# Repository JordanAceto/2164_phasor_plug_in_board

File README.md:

# NOTE: development of all VCF plug-in boards has been moved here https://github.com/JordanAceto/VCF_plug_in_boards
### This repo will no longer be updated. Follow the above link for the most current files.

# 2164 Phasor Plug-In Board

Small 6 stage SSM2164 based phase shifter PCB, designed to plug into a larger motherboard.

## Details

Six stage phase shifter implemented with SSM2164/V2164/SSI2164 quad VCAs. This PCB includes the audio path and CV inputs for frequency and feedback, but does not include any modulation sources.

The intended use for this board is to plug in to a larger motherboard which contains slots for two of these plug-in boards, as well as modulation sources, panel controls, and input/output routing. This motherboard could accept different filter boards sharing this footprint and header layout, for realizing stereo effects of various flavors.

## Inputs

-Audio in: dry audio input to be phase shifted.

-Frequency CV in: 0 volts to +2.048 volts, higher voltage = higher sweep.

-Feedback CV in: 0 volts to +2.048 volts, higher voltage = more feedback.

## Outputs

-Audio out: phase shifted audio output.

## Power Supply Requirements

A bipolar 12 volt power supply is needed. This will typically come from the motherboard.

## Calibration

-RV1 (depth trim): trims the depth of incoming frequency CV signals. Turn CW for greater depth and CCW for less depth. Adjust to taste.

-RV2 (center trim): trims the center frequency of the phase shifter. Turn CW for higher center frequency and CCW for lower center frequency. Adjust to taste.

-RV3 (feedback trim): trims the maximum amount of feedback. Turn CW for more maximum feedback and CCW for less maximum feedback. Exercise caution when adjusting this, as extreme settings can result in loud oscillations which could damage your ears or speakers if you are monitoring the sound with a loud amplifier. If you set this trimmer to be right on the edge of oscillation when about +2 volts is applied to the feedback CV input then make sure to sweep the frequency through its entire range, as a setting that doesn't squeal at certain frequency settings may squeal at other settings.

## Parts Ordering
The BOM has a link to a Mouser project with the majority of the parts needed to build the board, with the exception of the 2164 VCA chips. There is a link to the SmallBear Electronics parts page for these.

After the PCB is evaluated, the BOM will have a link to OSHPark, where you can order boards.

Zipped gerber files will be located in kicad_docs.

## License
CC by 4.0

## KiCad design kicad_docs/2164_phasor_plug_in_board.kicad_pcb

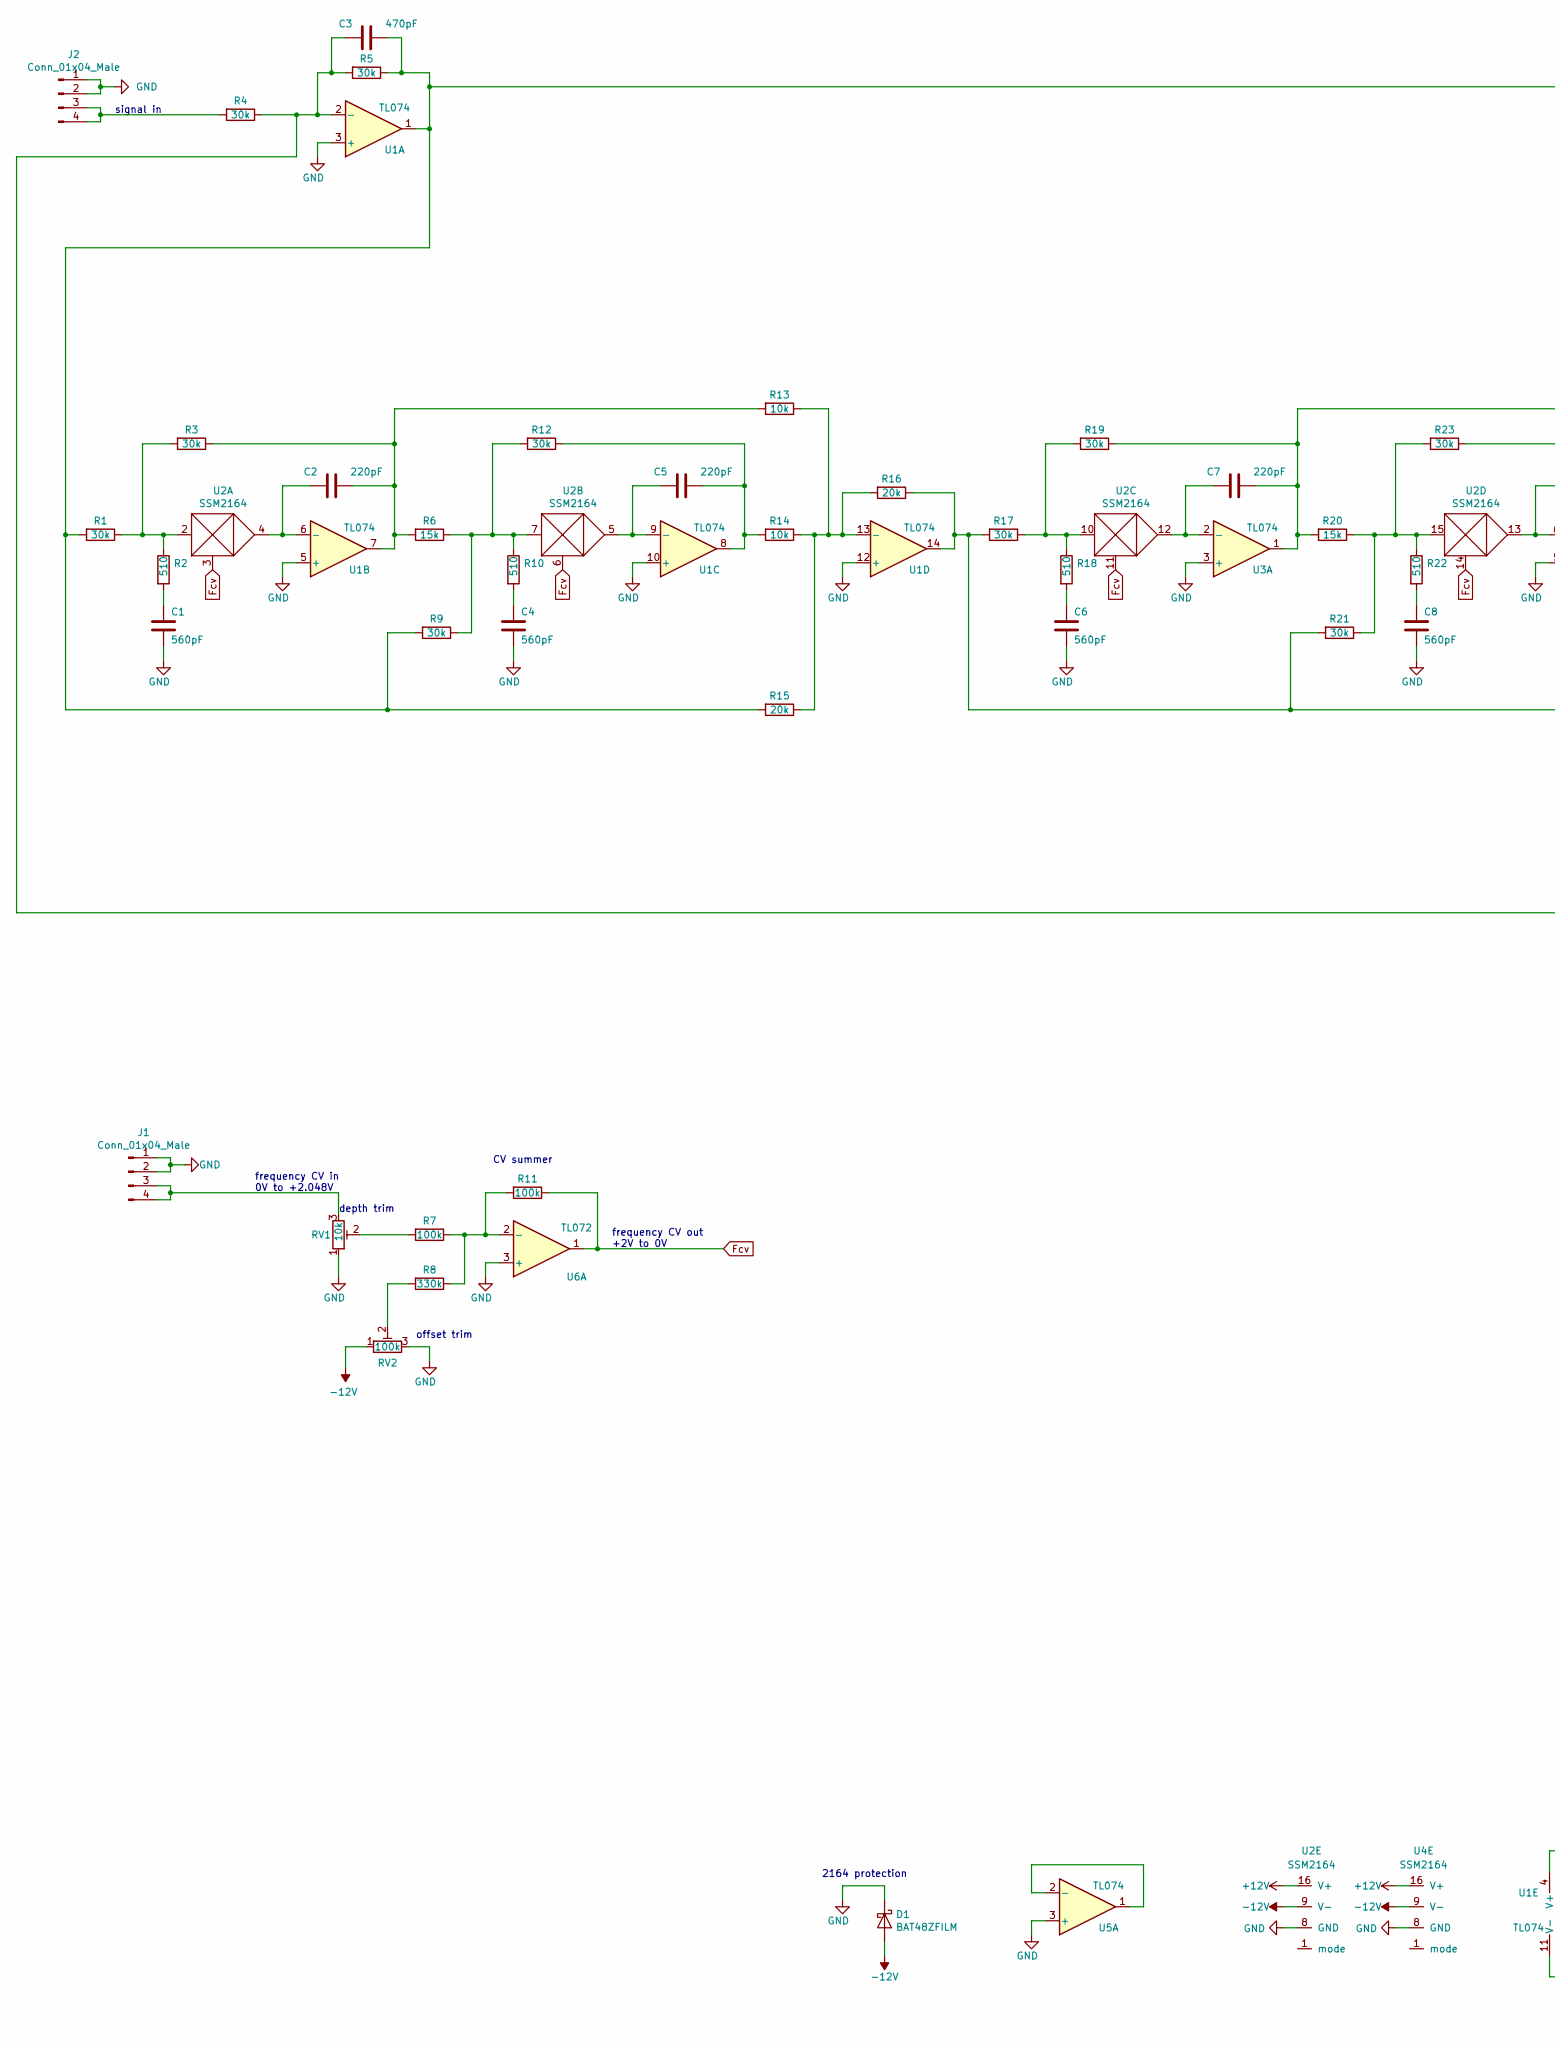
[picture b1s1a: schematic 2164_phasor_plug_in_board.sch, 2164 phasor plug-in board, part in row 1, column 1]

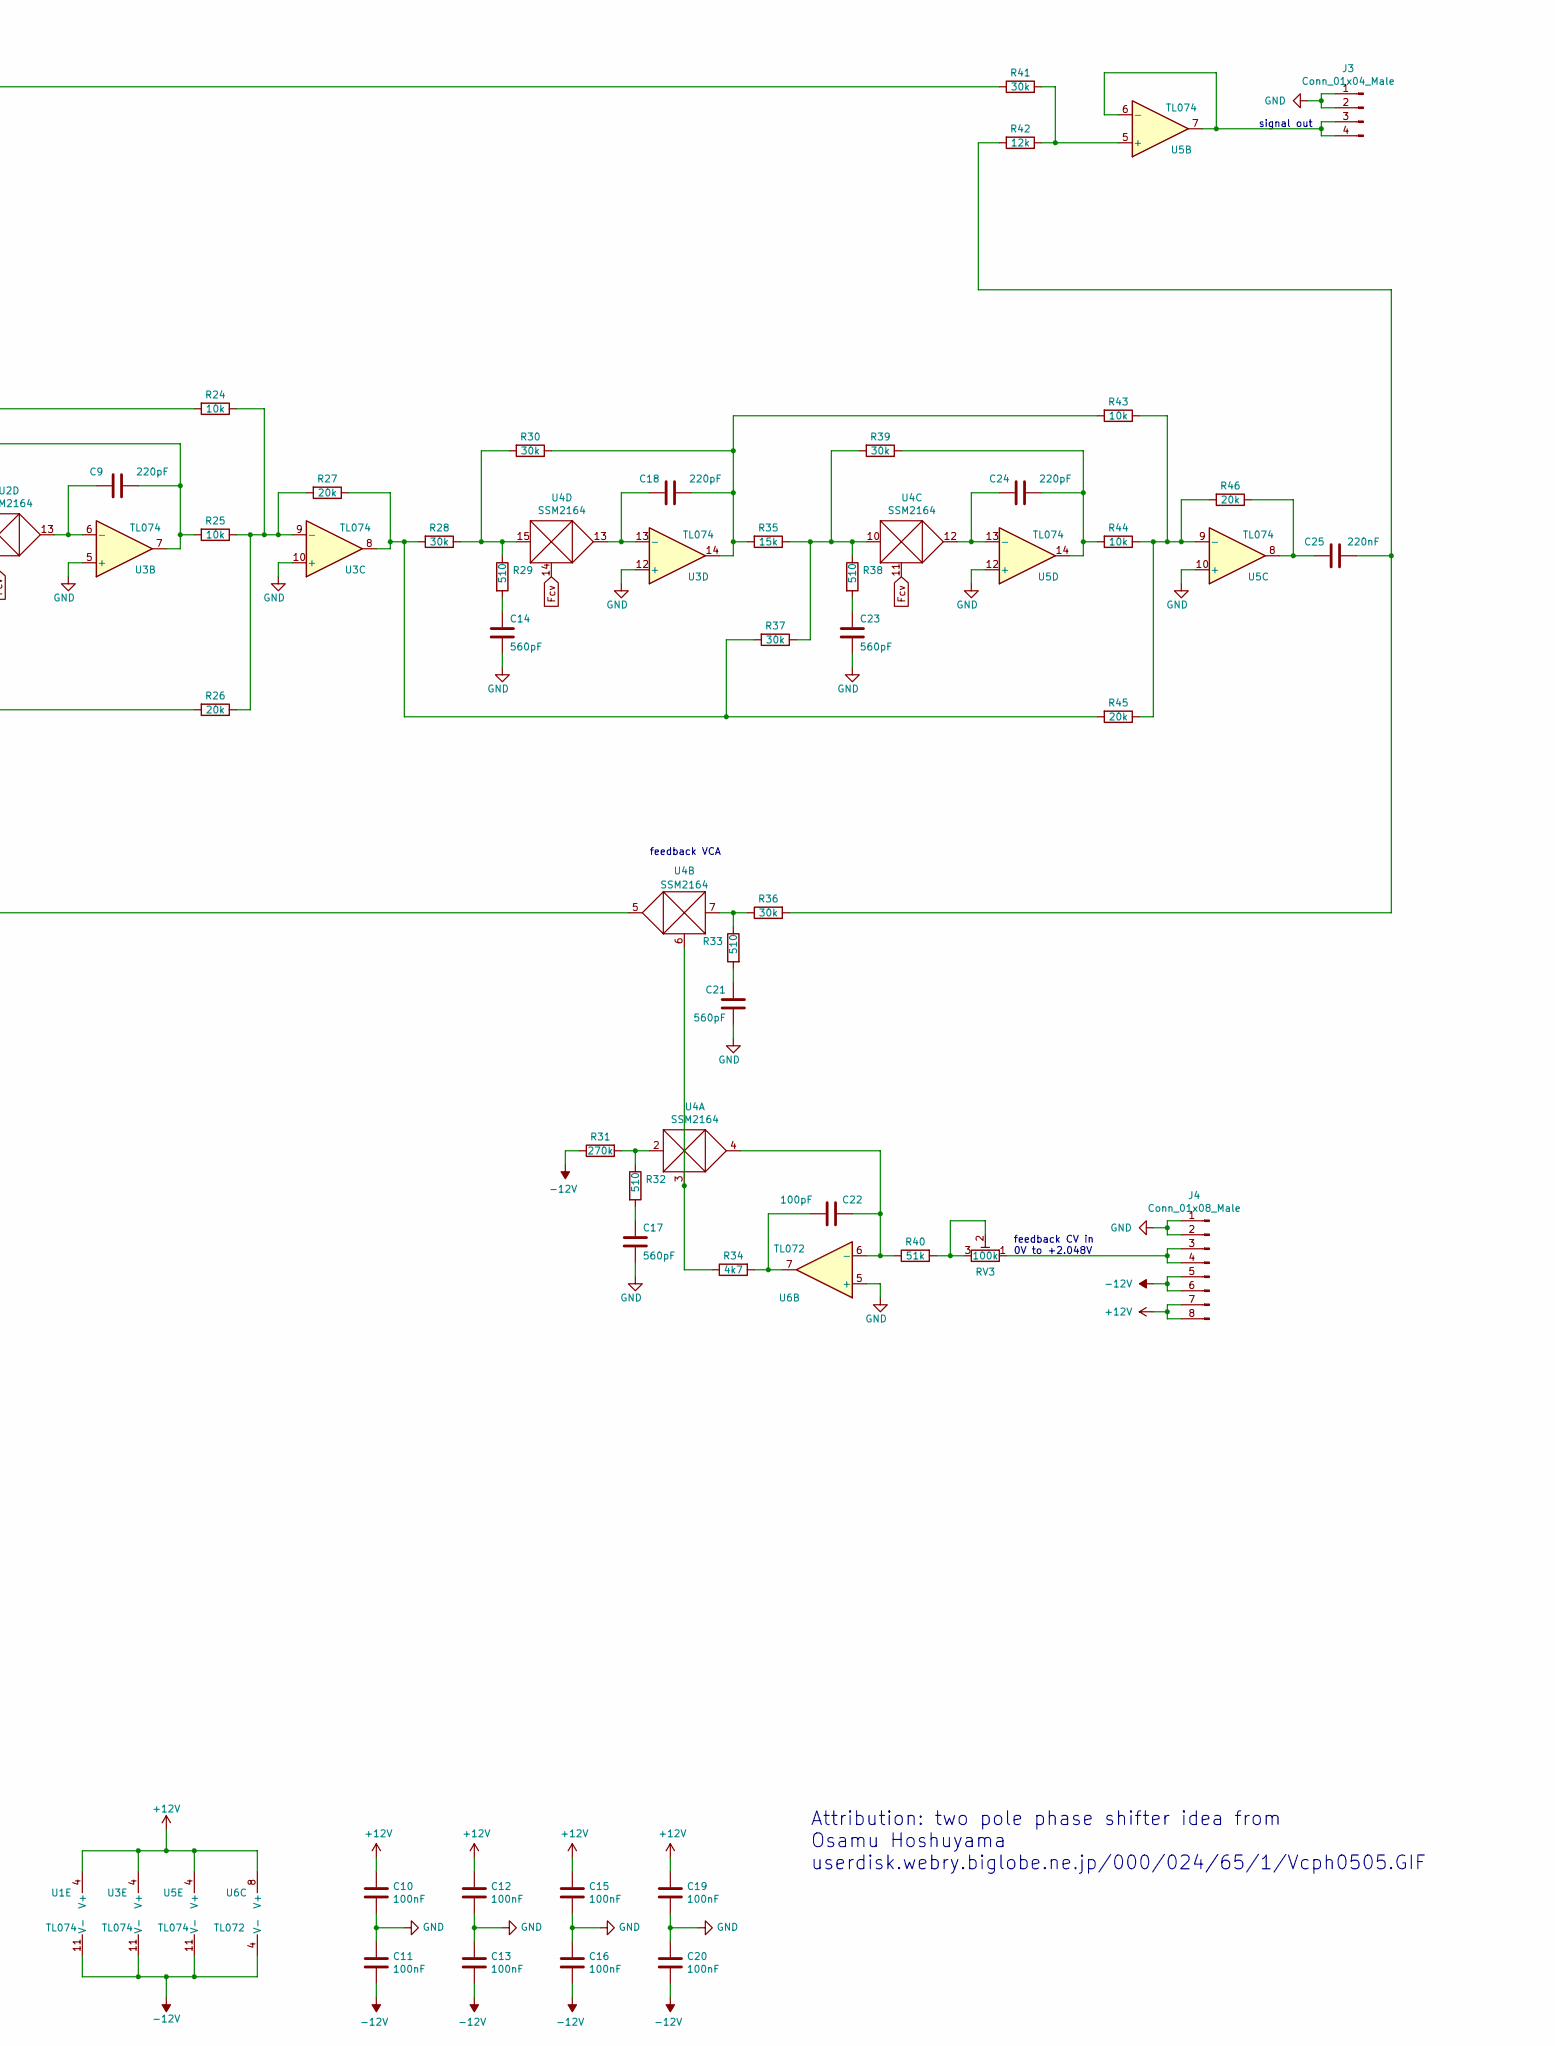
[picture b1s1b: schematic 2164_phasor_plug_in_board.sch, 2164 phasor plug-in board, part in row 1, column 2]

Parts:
C1, C4, C6, C8, C14, C17, C21, C23: 560pF; C_0805_2012Metric_Pad1.15x1.40mm_HandSolder
C2, C5, C7, C9, C18, C24: 220pF; C_0805_2012Metric_Pad1.15x1.40mm_HandSolder
C3: 470pF; C_0805_2012Metric_Pad1.15x1.40mm_HandSolder
C10, C11, C12, C13, C15, C16, C19, C20: 100nF; C_0805_2012Metric_Pad1.15x1.40mm_HandSolder
C22: 100pF; C_0805_2012Metric_Pad1.15x1.40mm_HandSolder
C25: 220nF; C_1206_3216Metric_Pad1.42x1.75mm_HandSolder
D1: BAT48ZFILM; D_SOD-123
J1, J2, J3: Conn_01x04_Male; PinHeader_1x04_P2.54mm_Vertical
J4: Conn_01x08_Male; PinHeader_1x08_P2.54mm_Vertical
R1, R3, R4, R5, R9, R12, R17, R19, R21, R23, R28, R30, R36, R37, R39, R41: 30k; R_0805_2012Metric_Pad1.15x1.40mm_HandSolder
R2, R10, R18, R22, R29, R32, R33, R38: 510; R_0805_2012Metric_Pad1.15x1.40mm_HandSolder
R6, R20, R35: 15k; R_0805_2012Metric_Pad1.15x1.40mm_HandSolder
R7, R11: 100k; R_0805_2012Metric_Pad1.15x1.40mm_HandSolder
R8: 330k; R_0805_2012Metric_Pad1.15x1.40mm_HandSolder
R13, R14, R24, R25, R43, R44: 10k; R_0805_2012Metric_Pad1.15x1.40mm_HandSolder
R15, R16, R26, R27, R45, R46: 20k; R_0805_2012Metric_Pad1.15x1.40mm_HandSolder
R31: 270k; R_0805_2012Metric_Pad1.15x1.40mm_HandSolder
R34: 4k7; R_0805_2012Metric_Pad1.15x1.40mm_HandSolder
R40: 51k; R_0805_2012Metric_Pad1.15x1.40mm_HandSolder
R42: 12k; R_0805_2012Metric_Pad1.15x1.40mm_HandSolder
RV1: 10k; Potentiometer_Bourns_3269W_Vertical
RV2, RV3: 100k; Potentiometer_Bourns_3269W_Vertical
U1, U3, U5: TL074; SOIC-14_3.9x8.7mm_P1.27mm
U2, U4: SSM2164; SOIC-16_3.9x9.9mm_P1.27mm
U6: TL072; SOIC-8_3.9x4.9mm_P1.27mm

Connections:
+12V: C10.1, C12.1, C15.1, C19.1, J4.7, J4.8, U1.4 (V+), U2.16 (V+), U3.4 (V+), U4.16 (V+), U5.4 (V+), U6.8 (V+)
-12V: C11.2, C13.2, C16.2, C20.2, D1.2 (A), J4.5, J4.6, R31.1, RV2.1, U1.11 (V-), U2.9 (V-), U3.11 (V-), U4.9 (V-), U5.11 (V-), U6.4 (V-)
Fcv: R11.1, U2.3, U2.6, U2.11, U2.14, U4.11, U4.14, U6.1
GND: C1.2, C4.2, C6.2, C8.2, C10.2, C11.1, C12.2, C13.1, C14.2, C15.2, C16.1, C17.2, C19.2, C20.1, C21.2, C23.2, D1.1 (K), J1.1, J1.2, J2.1, J2.2, J3.1, J3.2, J4.1, J4.2, RV1.1, RV2.3, U1.3 (+), U1.5 (+), U1.10 (+), U1.12 (+), U2.8 (GND), U3.3 (+), U3.5 (+), U3.10 (+), U3.12 (+), U4.8 (GND), U5.3 (+), U5.10 (+), U5.12 (+), U6.3 (+), U6.5 (+)
unnamed: C1.1, R2.2
unnamed: C2.1, R3.1, R6.2, R13.2, U1.7
unnamed: C2.2, U1.6 (-), U2.4
unnamed: C3.1, R1.2, R5.1, R9.2, R15.2, R41.1, U1.1
unnamed: C3.2, R4.1, R5.2, U1.2 (-), U4.5
unnamed: C4.1, R10.2
unnamed: C5.1, R12.1, R14.2, U1.8
unnamed: C5.2, U1.9 (-), U2.5
unnamed: C6.1, R18.2
unnamed: C7.1, R19.1, R20.2, R24.2, U3.1
unnamed: C7.2, U2.12, U3.2 (-)
unnamed: C8.1, R22.2
unnamed: C9.1, R23.1, R25.2, U3.7
unnamed: C9.2, U2.13, U3.6 (-)
unnamed: C14.1, R29.2
unnamed: C17.1, R32.2
unnamed: C18.1, R30.1, R35.2, R43.2, U3.14
unnamed: C18.2, U3.13 (-), U4.13
unnamed: C21.1, R33.2
unnamed: C22.1, R34.2, U6.7
unnamed: C22.2, R40.1, U4.4, U6.6 (-)
unnamed: C23.1, R38.2
unnamed: C24.1, R39.1, R44.2, U5.14
unnamed: C24.2, U4.12, U5.13 (-)
unnamed: C25.1, R36.2, R42.2
unnamed: C25.2, R46.1, U5.8
unnamed: J1.3, J1.4, RV1.3
unnamed: J2.3, J2.4, R4.2
unnamed: J3.3, J3.4, U5.6 (-), U5.7
unnamed: R1.1, R2.1, R3.2, U2.2
unnamed: R7.2, RV1.2
unnamed: R8.2, RV2.2
unnamed: R6.1, R9.1, R10.1, R12.2, U2.7
unnamed: R7.1, R8.1, R11.2, U6.2 (-)
unnamed: R13.1, R14.1, R15.1, R16.2, U1.13 (-)
unnamed: R16.1, R17.2, R21.2, R26.2, U1.14
unnamed: R17.1, R18.1, R19.2, U2.10
unnamed: R20.1, R21.1, R22.1, R23.2, U2.15
unnamed: R24.1, R25.1, R26.1, R27.2, U3.9 (-)
unnamed: R27.1, R28.2, R37.2, R45.2, U3.8
unnamed: R28.1, R29.1, R30.2, U4.15
unnamed: R31.2, R32.1, U4.2
unnamed: R33.1, R36.1, U4.7
unnamed: R34.1, U4.3, U4.6
unnamed: R35.1, R37.1, R38.1, R39.2, U4.10
unnamed: R41.2, R42.1, U5.5 (+)
unnamed: R43.1, R44.1, R45.1, R46.2, U5.9 (-)
unnamed: U5.1, U5.2 (-)

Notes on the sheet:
offset trim
depth trim
frequency CV in 0V to +2.048V
signal in
signal out
feedback CV in 0V to +2.048V
frequency CV out +2V to 0V
Attribution: two pole phase shifter idea from Osamu Hoshuyama userdisk.webry.biglobe.ne.jp/000/024/65/1/Vcph0505.GIF
2164 protection
feedback VCA
CV summer

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
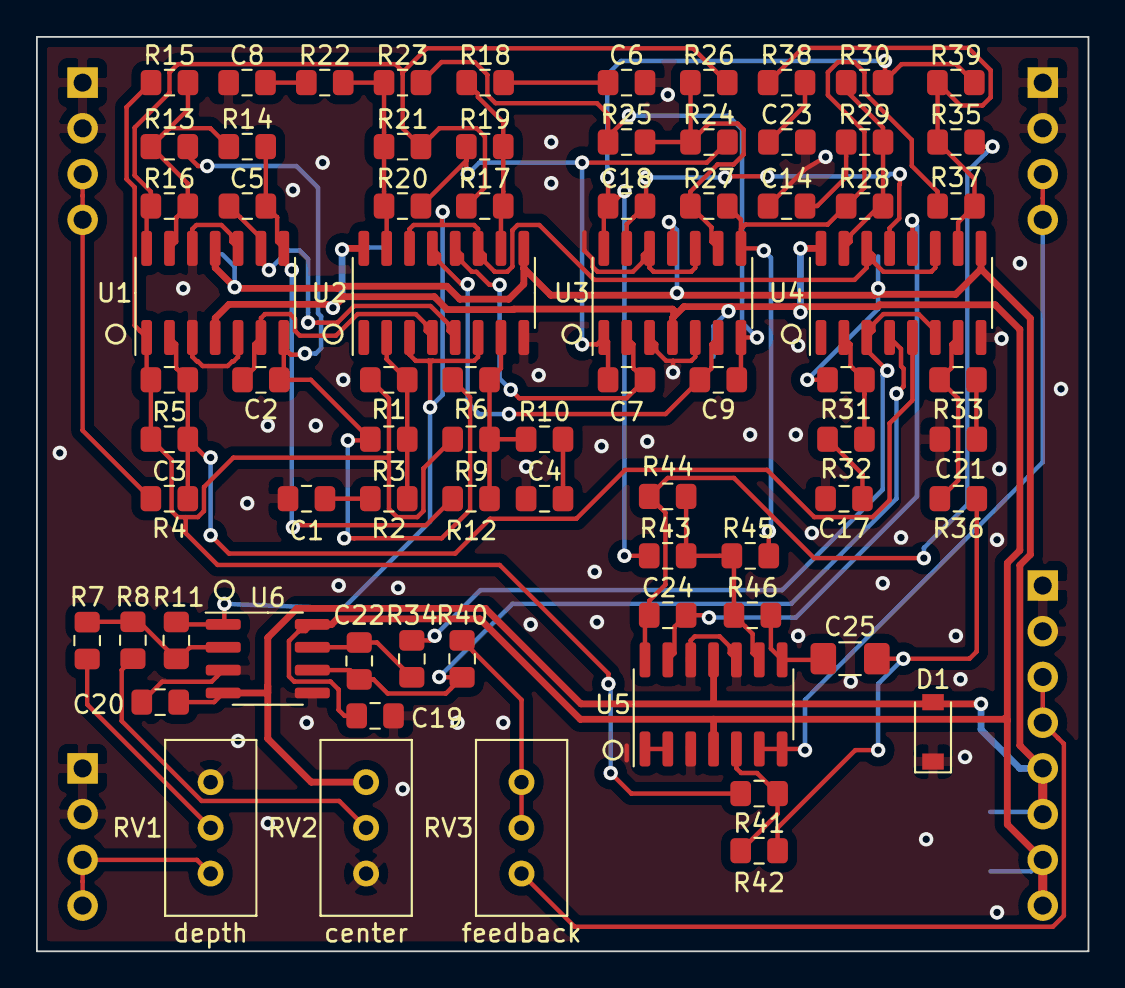
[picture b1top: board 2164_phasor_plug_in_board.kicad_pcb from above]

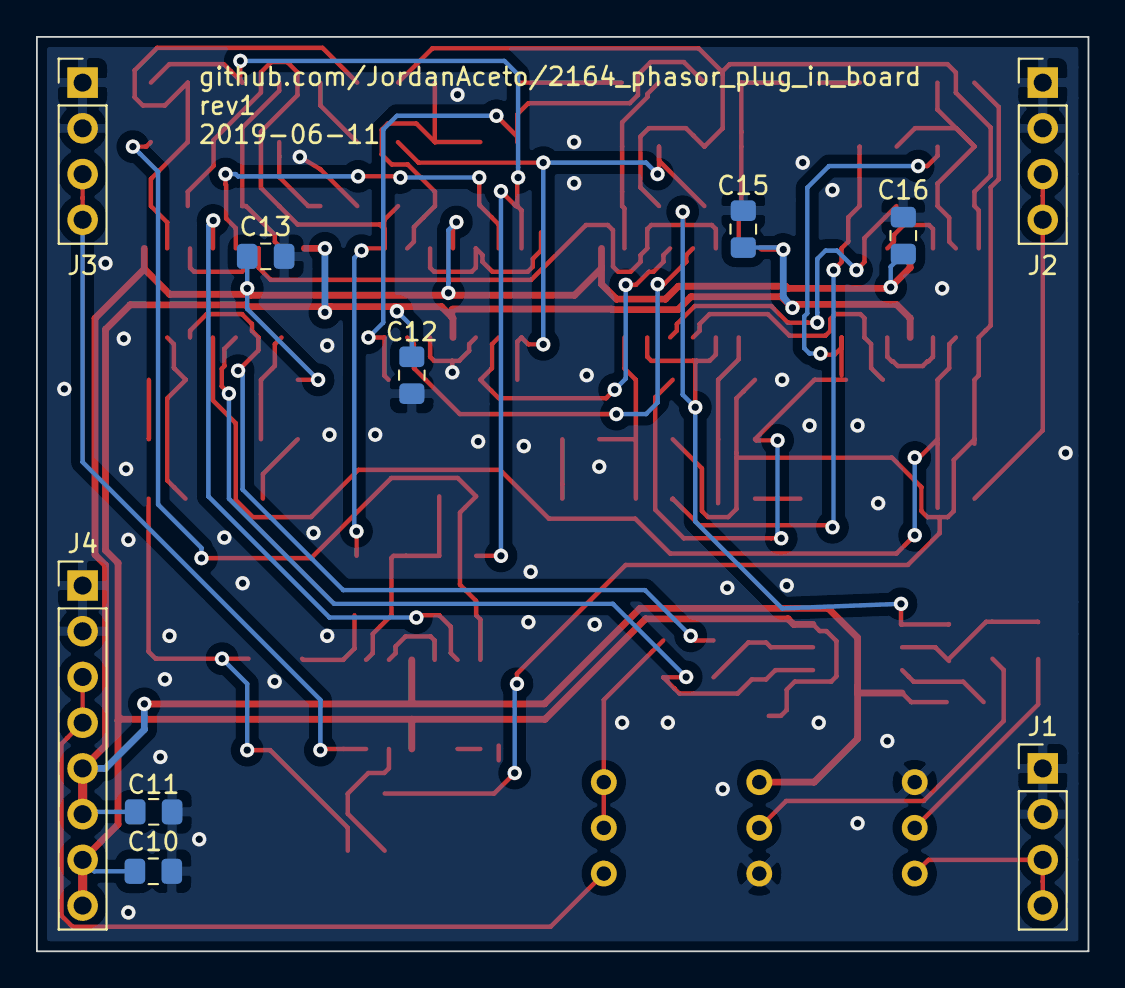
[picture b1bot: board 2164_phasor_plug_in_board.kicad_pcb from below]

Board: 2 copper layers, 58.4 x 50.8 mm, 85 parts (10 on the bottom side), 54 nets.

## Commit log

2019-06-11 add github url to board, add pic of board bottom
2019-06-11 add link to mouser project in BOM, update README
2019-06-11 add parts list to construction docs
2019-07-10 change trimmers to cheaper TH type
2019-07-10 update board pics to reflect TH trimmers
2019-07-10 update BOM with cheaper TH trimmers
2020-08-01 update readme to link to new repo

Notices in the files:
kicad_docs/2164_phasor_plug_in_board.sch:
creativecommons.org/licenses/by/4.0
